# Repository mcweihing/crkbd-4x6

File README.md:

An adaptation of the crkbd keyboard. It contains a 4x6 matrix and three thumb keys. It's also MX and Choc hotswappable.

All of the KiCad files needed to print the pcb are included. I know that the gerber files included are enough to print through JLCPCB.

I have dxf files to get plates made for the pcb's, but I won't have access to that computer for at least a week or two. Same with QMK.

If you want to do QMK yourself before I add it, I'll try to give the steps as best as I remember them.
There's a file which specifies rows and columns. Here, change it from 8 to 10. There's also a file which specifies input and output pins. There should be a list for rows which has D4, C6, D7, and E6. Add B4 to this. Now, you can add an extra row in the key layout and compile.

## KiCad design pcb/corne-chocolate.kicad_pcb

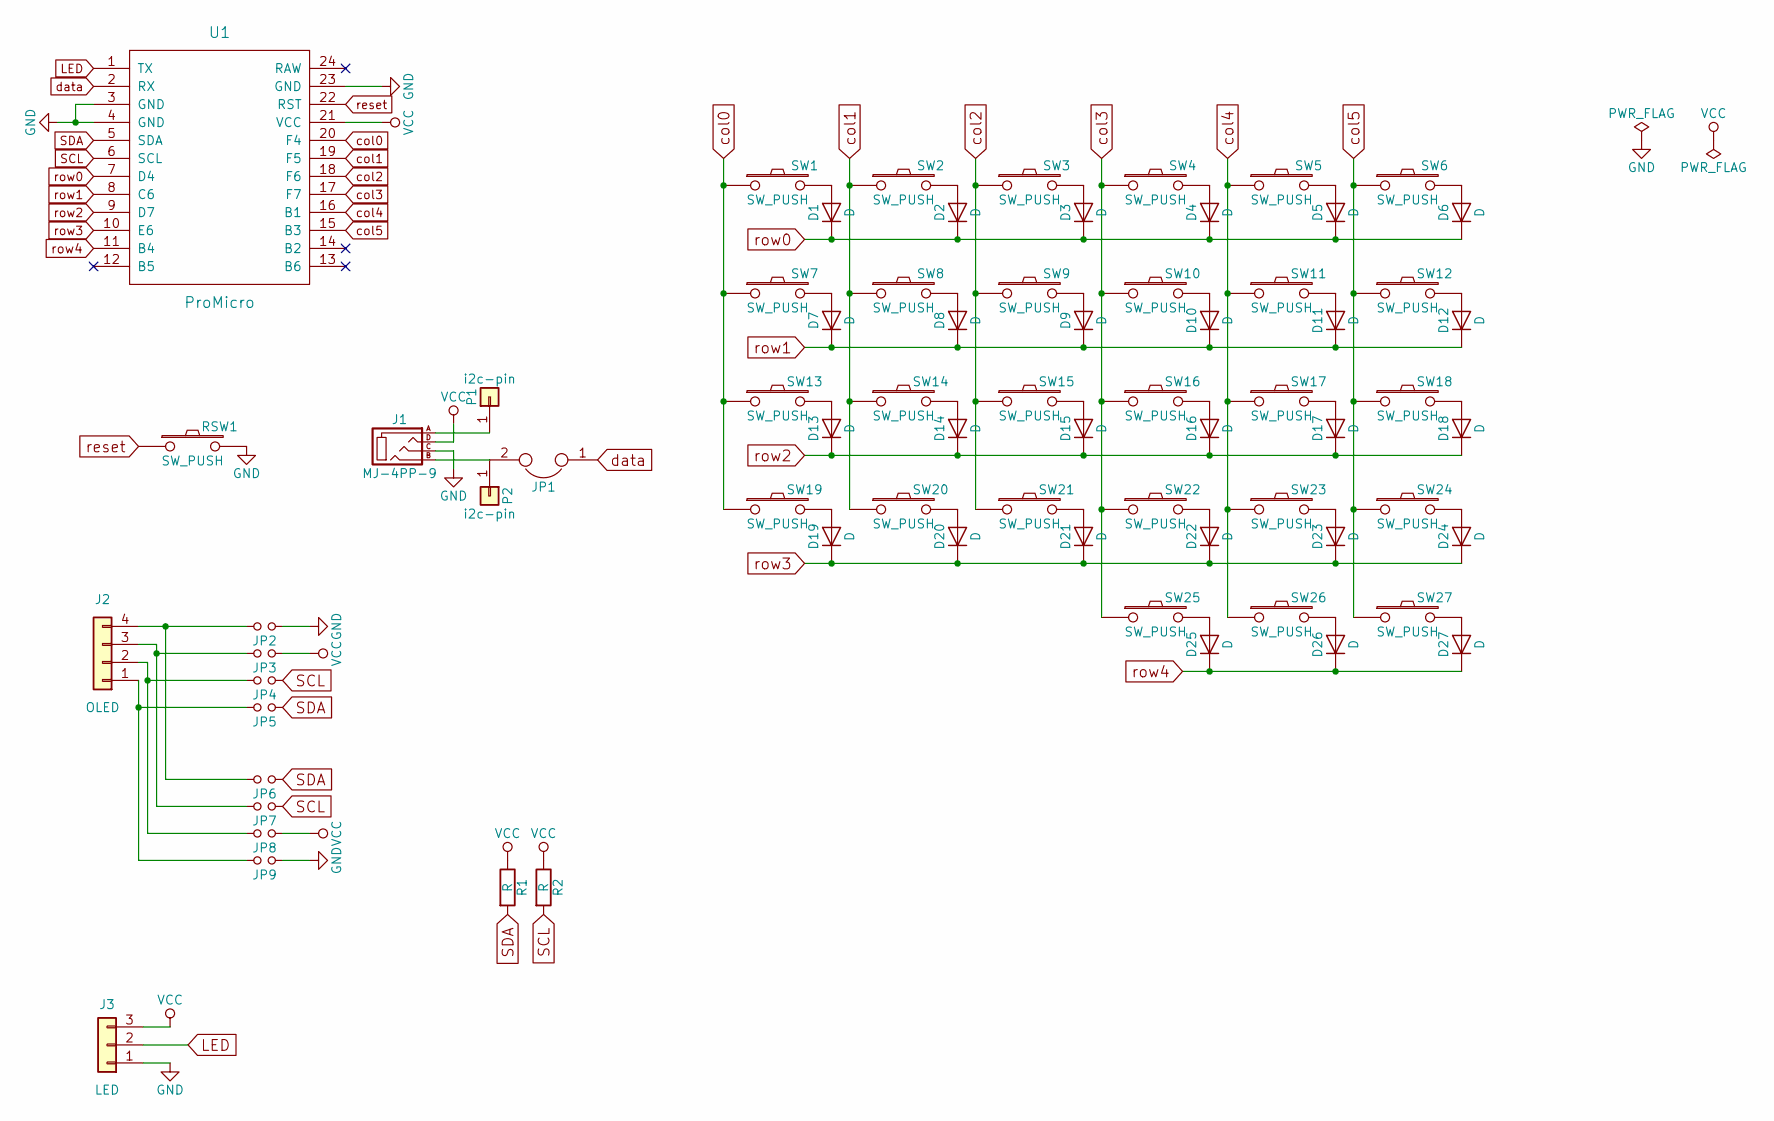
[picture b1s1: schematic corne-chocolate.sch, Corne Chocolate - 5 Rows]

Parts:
D1, D2, D3, D4, D5, D6, D7, D8, D9, D10, D11, D12, D13, D14, D15, D16, D17, D18, D19, D20, D21, D22, D23, D24, D25, D26, D27: D; D3_TH
J1: MJ-4PP-9
J2: OLED
J3: LED; StripLED_rev
JP1: JPC2
JP2, JP3, JP4, JP5, JP6, JP7, JP8, JP9: Jumper
P1, P2: i2c-pin; 1pin_conn
R1, R2: R
RSW1: SW_PUSH; ResetSW
SW1, SW2, SW3, SW4, SW5, SW6, SW7, SW8, SW9, SW10, SW11, SW12, SW13, SW14, SW15, SW16, SW17, SW18, SW19, SW20, SW21, SW22, SW23, SW24, SW25, SW26: SW_PUSH; CherryMX_Choc_Hotswap
SW27: SW_PUSH; CherryMX_Choc_Hotswap_1.5u
U1: ProMicro; ProMicro_v2

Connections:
GND: J1.C, J3.1, JP2.1, JP9.1, RSW1.2, U1.3 (GND), U1.4 (GND), U1.23 (GND)
LED: J3.2, U1.1 (TX)
unnamed: D1.2 (A), SW1.2
unnamed: D2.2 (A), SW2.2
unnamed: D3.2 (A), SW3.2
unnamed: D4.2 (A), SW4.2
unnamed: D5.2 (A), SW5.2
unnamed: D6.2 (A), SW6.2
unnamed: D7.2 (A), SW7.2
unnamed: D8.2 (A), SW8.2
unnamed: D9.2 (A), SW9.2
unnamed: D10.2 (A), SW10.2
unnamed: D11.2 (A), SW11.2
unnamed: D12.2 (A), SW12.2
unnamed: D13.2 (A), SW13.2
unnamed: D14.2 (A), SW14.2
unnamed: D15.2 (A), SW15.2
unnamed: D16.2 (A), SW16.2
unnamed: D17.2 (A), SW17.2
unnamed: D18.2 (A), SW18.2
unnamed: D19.2 (A), SW19.2
unnamed: D20.2 (A), SW20.2
unnamed: D21.2 (A), SW21.2
unnamed: D22.2 (A), SW22.2
unnamed: D23.2 (A), SW23.2
unnamed: D24.2 (A), SW24.2
unnamed: D25.2 (A), SW25.2
unnamed: D26.2 (A), SW26.2
unnamed: D27.2 (A), SW27.2
unnamed: J1.A, P1.1
unnamed: J1.B, JP1.2, P2.1
unnamed: J2.1, JP5.2, JP9.2
unnamed: J2.2, JP4.2, JP8.2
unnamed: J2.3, JP3.2, JP7.2
unnamed: J2.4, JP2.2, JP6.2
SCL: JP4.1, JP7.1, R2.2, U1.6 (SCL)
SDA: JP5.1, JP6.1, R1.2, U1.5 (SDA)
VCC: J1.D, J3.3, JP3.1, JP8.1, R1.1, R2.1, U1.21 (VCC)
col0: SW1.1, SW7.1, SW13.1, SW19.1, U1.20 (F4)
col1: SW2.1, SW8.1, SW14.1, SW20.1, U1.19 (F5)
col2: SW3.1, SW9.1, SW15.1, SW21.1, U1.18 (F6)
col3: SW4.1, SW10.1, SW16.1, SW22.1, SW25.1, U1.17 (F7)
col4: SW5.1, SW11.1, SW17.1, SW23.1, SW26.1, U1.16 (B1)
col5: SW6.1, SW12.1, SW18.1, SW24.1, SW27.1, U1.15 (B3)
data: JP1.1, U1.2 (RX)
reset: RSW1.1, U1.22 (RST)
row0: D1.1 (K), D2.1 (K), D3.1 (K), D4.1 (K), D5.1 (K), D6.1 (K), U1.7 (D4)
row1: D7.1 (K), D8.1 (K), D9.1 (K), D10.1 (K), D11.1 (K), D12.1 (K), U1.8 (C6)
row2: D13.1 (K), D14.1 (K), D15.1 (K), D16.1 (K), D17.1 (K), D18.1 (K), U1.9 (D7)
row3: D19.1 (K), D20.1 (K), D21.1 (K), D22.1 (K), D23.1 (K), D24.1 (K), U1.10 (E6)
row4: D25.1 (K), D26.1 (K), D27.1 (K), U1.11 (B4)

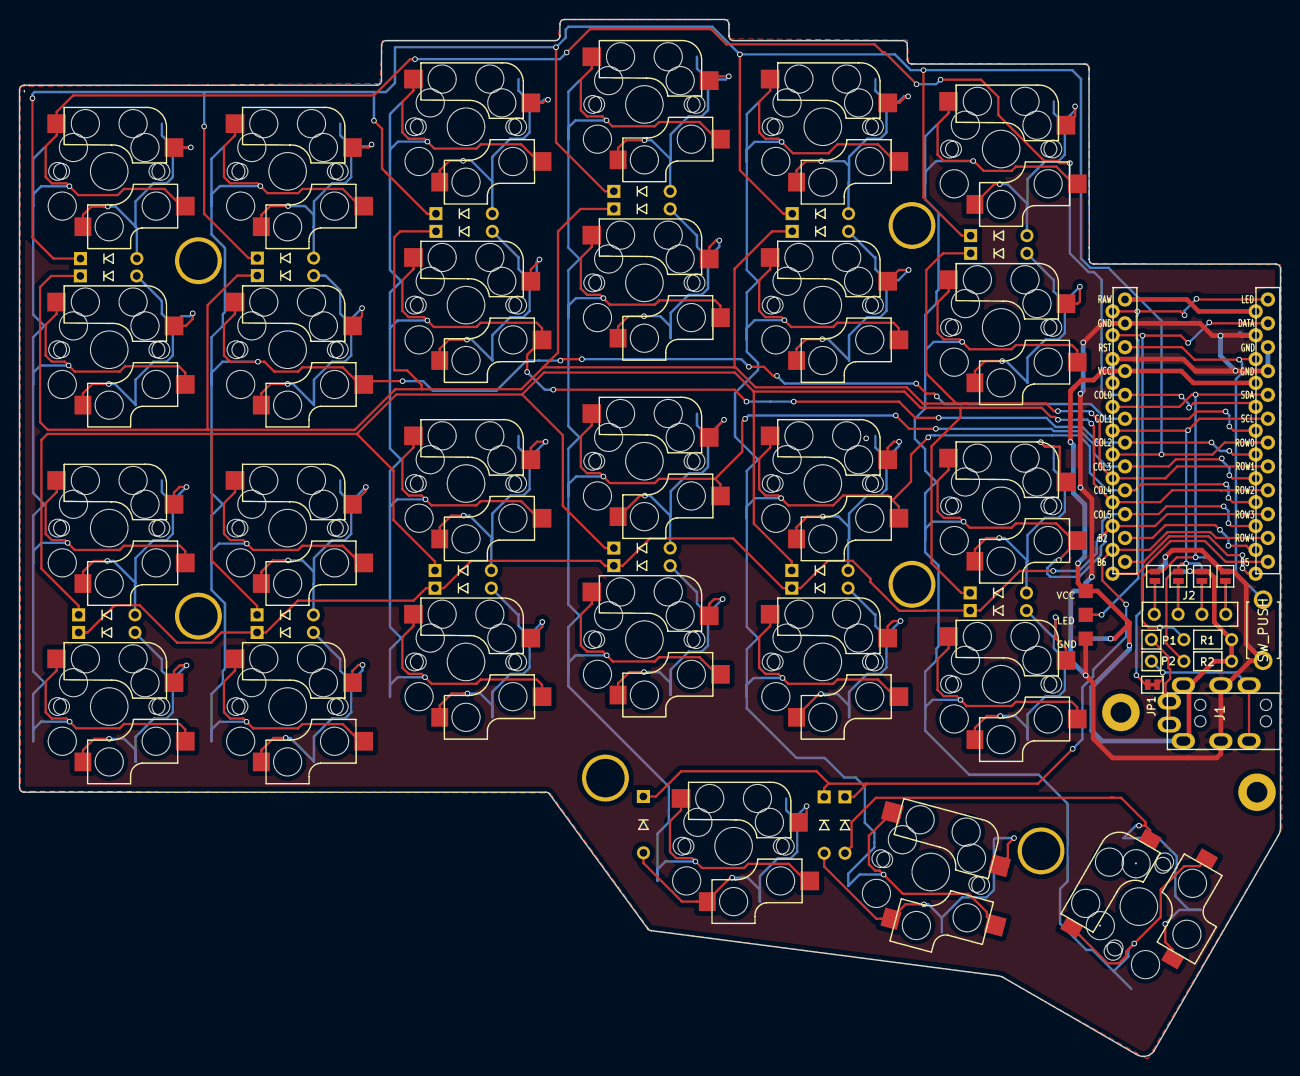
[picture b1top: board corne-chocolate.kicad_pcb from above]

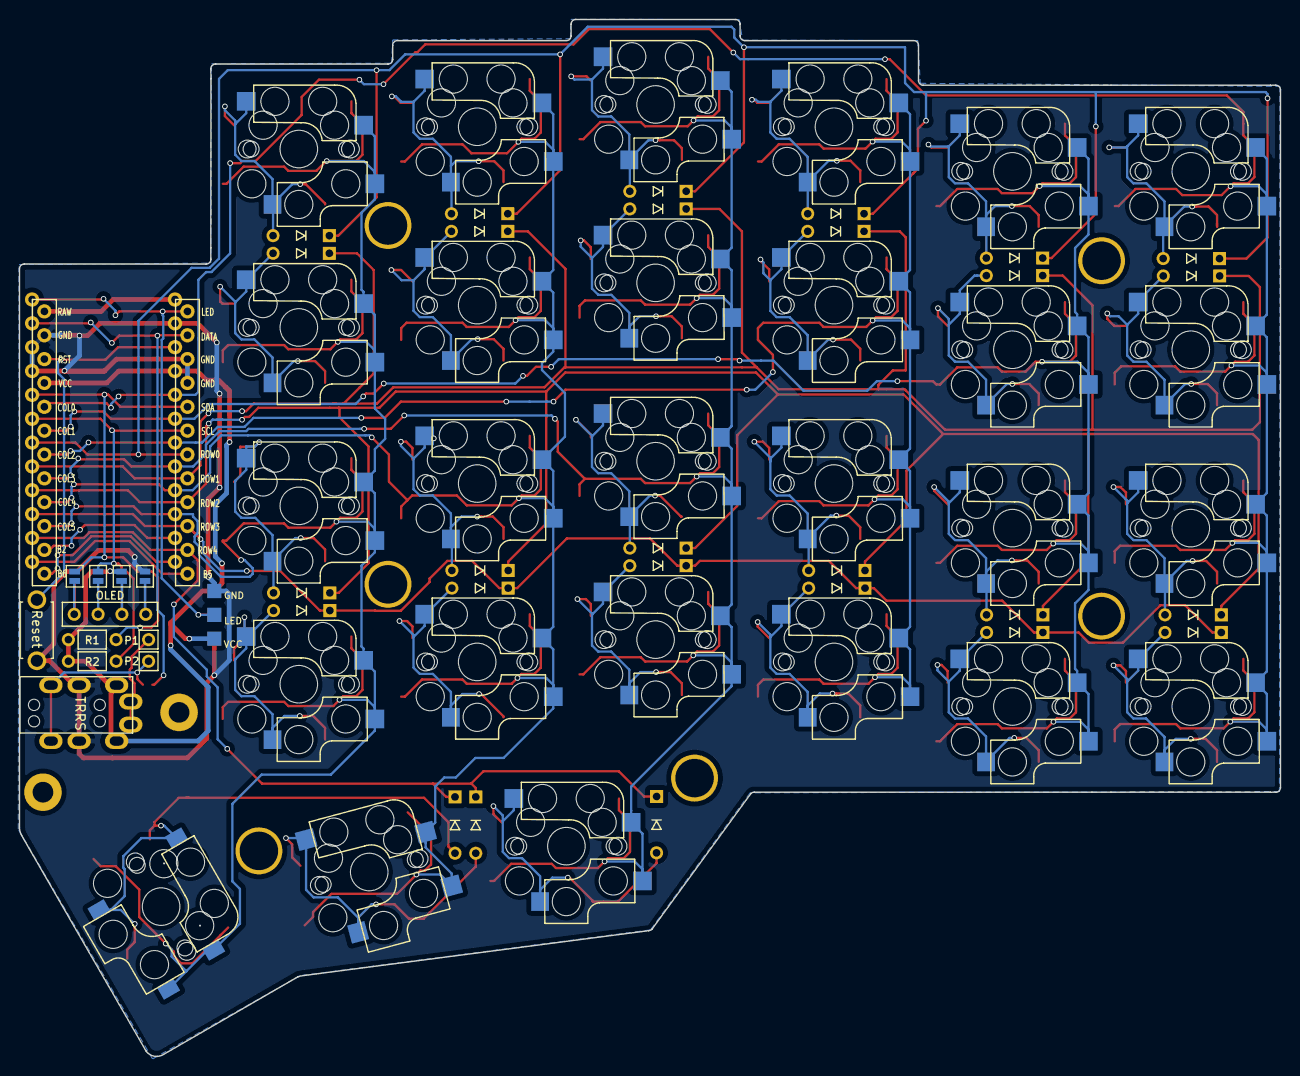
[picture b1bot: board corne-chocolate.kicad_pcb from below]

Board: 2 copper layers, 134.3 x 110.4 mm, 72 parts (4 on the bottom side), 51 nets.

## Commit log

2019-07-29 Added pcb files.
2019-07-29 Added a default qmk configuration
2019-08-26 added .dxf plate files
2019-08-26 Switch cutout footprints for MX and Choc
